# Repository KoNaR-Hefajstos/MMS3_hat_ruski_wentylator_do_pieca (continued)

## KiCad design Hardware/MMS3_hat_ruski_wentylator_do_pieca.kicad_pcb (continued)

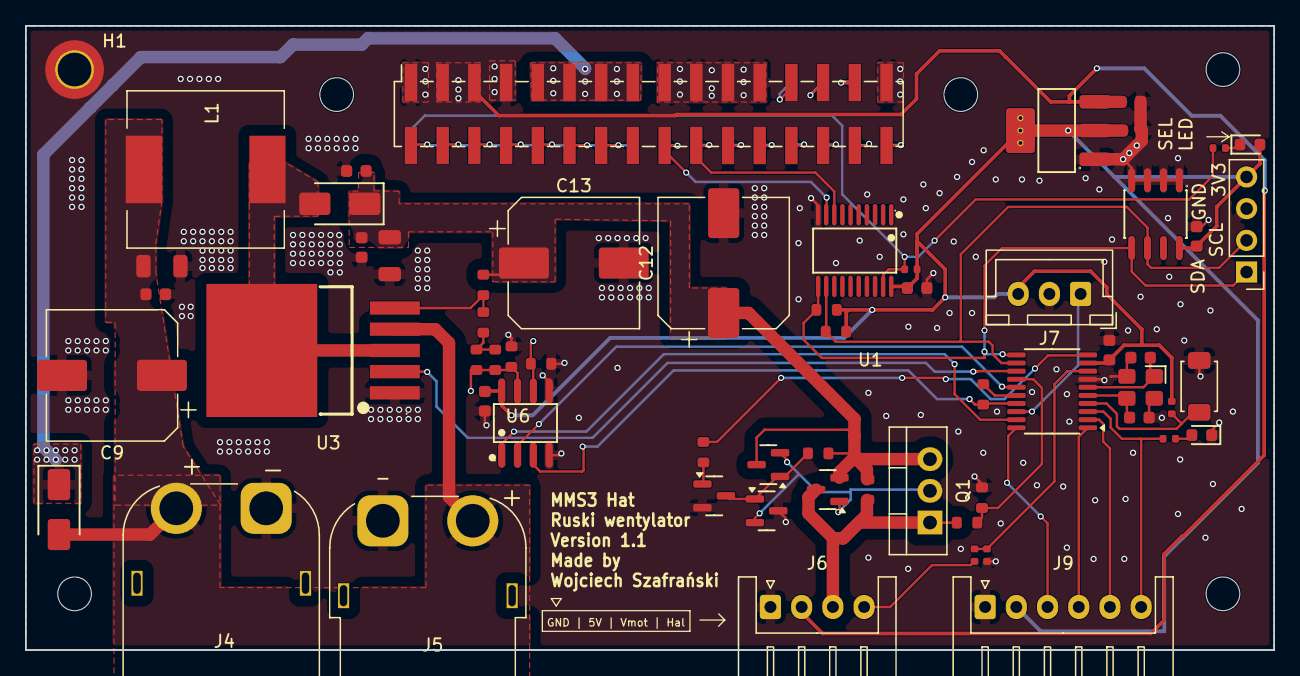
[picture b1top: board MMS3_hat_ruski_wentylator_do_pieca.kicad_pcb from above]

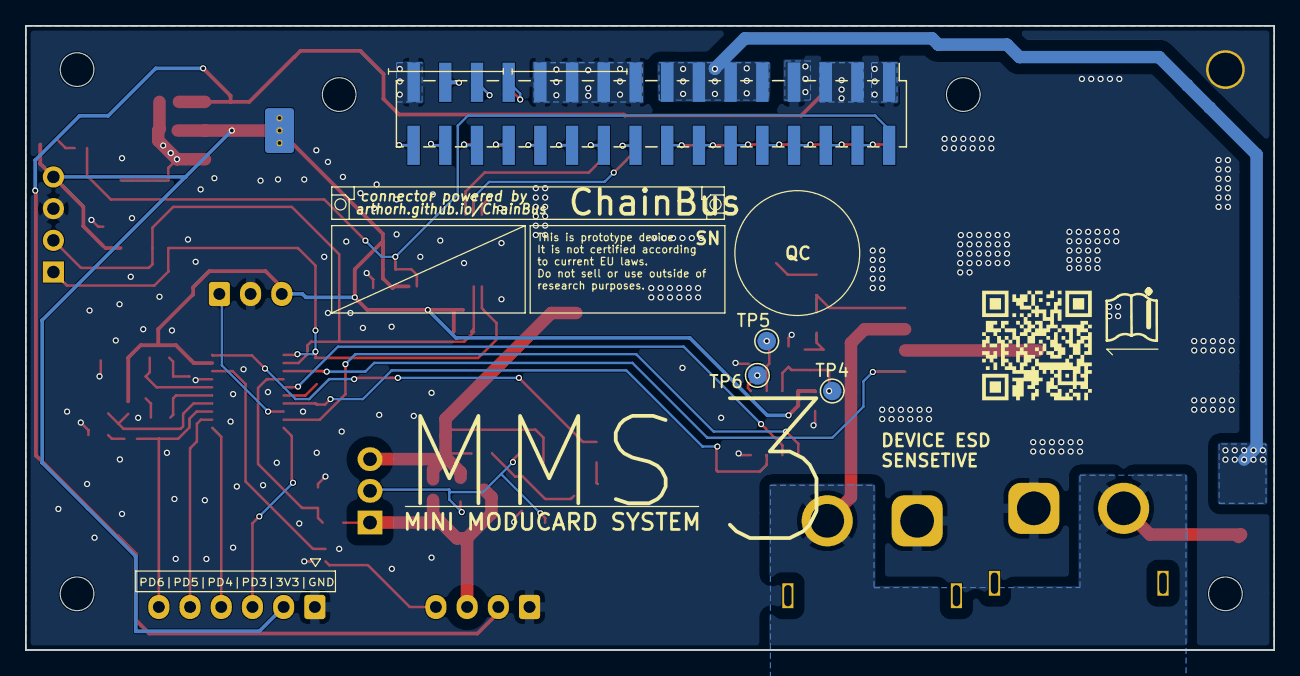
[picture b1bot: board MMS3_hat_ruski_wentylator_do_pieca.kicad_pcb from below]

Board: 2 copper layers, 100.0 x 50.0 mm, 71 parts (4 on the bottom side), 55 nets.

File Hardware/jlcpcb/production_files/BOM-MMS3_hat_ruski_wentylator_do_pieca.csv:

Comment,Designator,Footprint,LCSC,Quantity
0Ω,"R18,R6",R_0603,C21189,2
100nF,"C1,C2,C4,C6",C_0603,C14663,4
10kΩ,"R12,R19,R24",R_0402,C25744,3
10kΩ,"R2,R3",R_0603,C25804,2
10uF,"C14,C15",C_1206,C13585,2
10uF,"C16,C18",C_0603,C19702,2
12pF,"C3,C5",C_0603,C38523,2
15kΩ,R23,R_0402,C25756,1
1kΩ,"R16,R17,R5,R7",R_0603,C21190,4
1uF,"C10,C11,C17",C_0603,C15849,3
220Ω,R28,R_0603,C22962,1
2kΩ,R20,R_0603,C22975,1
330Ω,"R1,R13",R_0402,C25104,2
36kΩ,R4,R_0603,C23147,1
56kΩ,R14,R_0603,C23206,1
AMS1117,U4,SOT-223-3_L6.5-W3.4-P2.30-LS7.0-BR,C6186,1
AO3401A,Q10,Q_SOT-23,C15127,1
M24C64,U2,SOIC-8_L5.0-W4.0-P1.27-LS6.0-BL,C79988,1
M7,D1,D_SMA,C95872,1
MCP4161-502E/SN,U6,SOIC-8_L4.9-W3.9-P1.27-LS6.0-BL,C636080,1
MMBT5401 200-300,Q11,Q_SOT-23,C8326,1
MMBT5551 200-300,"Q12,Q9",Q_SOT-23,C2145,2
Red,"D3,D5",D_0603,C2286,2
SN74CB3Q3245PWR,U1,TSSOP-20_L6.5-W4.4-P0.65-LS6.4-BL,C470961,1
SS54,D2,D_SMA,C22452,1
"Tactile Button, 160gf",S1,SW_TS-1088-AR02016,C720477,1
Whatever the chinese man has (preferably 220uF),"C12,C13,C9",CP_Elec_10x10,C178727,3
X322525MOB4SI,X2,OSC-SMD_4P-L3.2-W2.5-BL,C9006,1
XL6019E1,U3,TO-263-5_L10.2-W9.9-P1.70-LS14.4-TL,C73018,1
Conn_01x06_Socket,J9,JST_XH_S6B-XH-A_1x06_P2.50mm_Horizontal,,1
Program,J7,JST_XH_B3B-XH-A_1x03_P2.50mm_Vertical,,1
Conn_01x04_Socket,J6,JST_XH_S4B-XH-A_1x04_P2.50mm_Horizontal,,1
Chainbus Out,J2,PinSocket_2x16_P2.54mm_Vertical_SMD,,1
PMOS,Q1,TO-220-3_Vertical,,1
Conn_01x04_Pin,J3,PinHeader_1x04_P2.54mm_Vertical,,1
47uH 5A,L1,L_12x12mm_H6mm,,1
CH32V003FxPx,U5,TSSOP-20_4.4x6.5mm_P0.65mm,,1
TestPoint,TP5,TestPoint_Pad_D1.5mm,,1
Chainbus in,J1,PinHeader_2x16_P2.54mm_Vertical_SMD,,1
TestPoint,TP4,TestPoint_Pad_D1.5mm,,1
TestPoint,TP6,TestPoint_Pad_D1.5mm,,1

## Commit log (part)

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2026-04-29 finished schematic
2026-05-01 inital layout
2026-05-04 commit before removing all the diodes :"
2026-05-04 finished routing
2026-05-05 minor fixes etc
2026-06-08 BREAKING: updated CH32v003 programming pinout
2026-06-10 added documentation
